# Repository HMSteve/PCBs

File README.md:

# Eine Sammlung von PCBs

Hier finden sich Platinen fuer verschiedene Projekte.

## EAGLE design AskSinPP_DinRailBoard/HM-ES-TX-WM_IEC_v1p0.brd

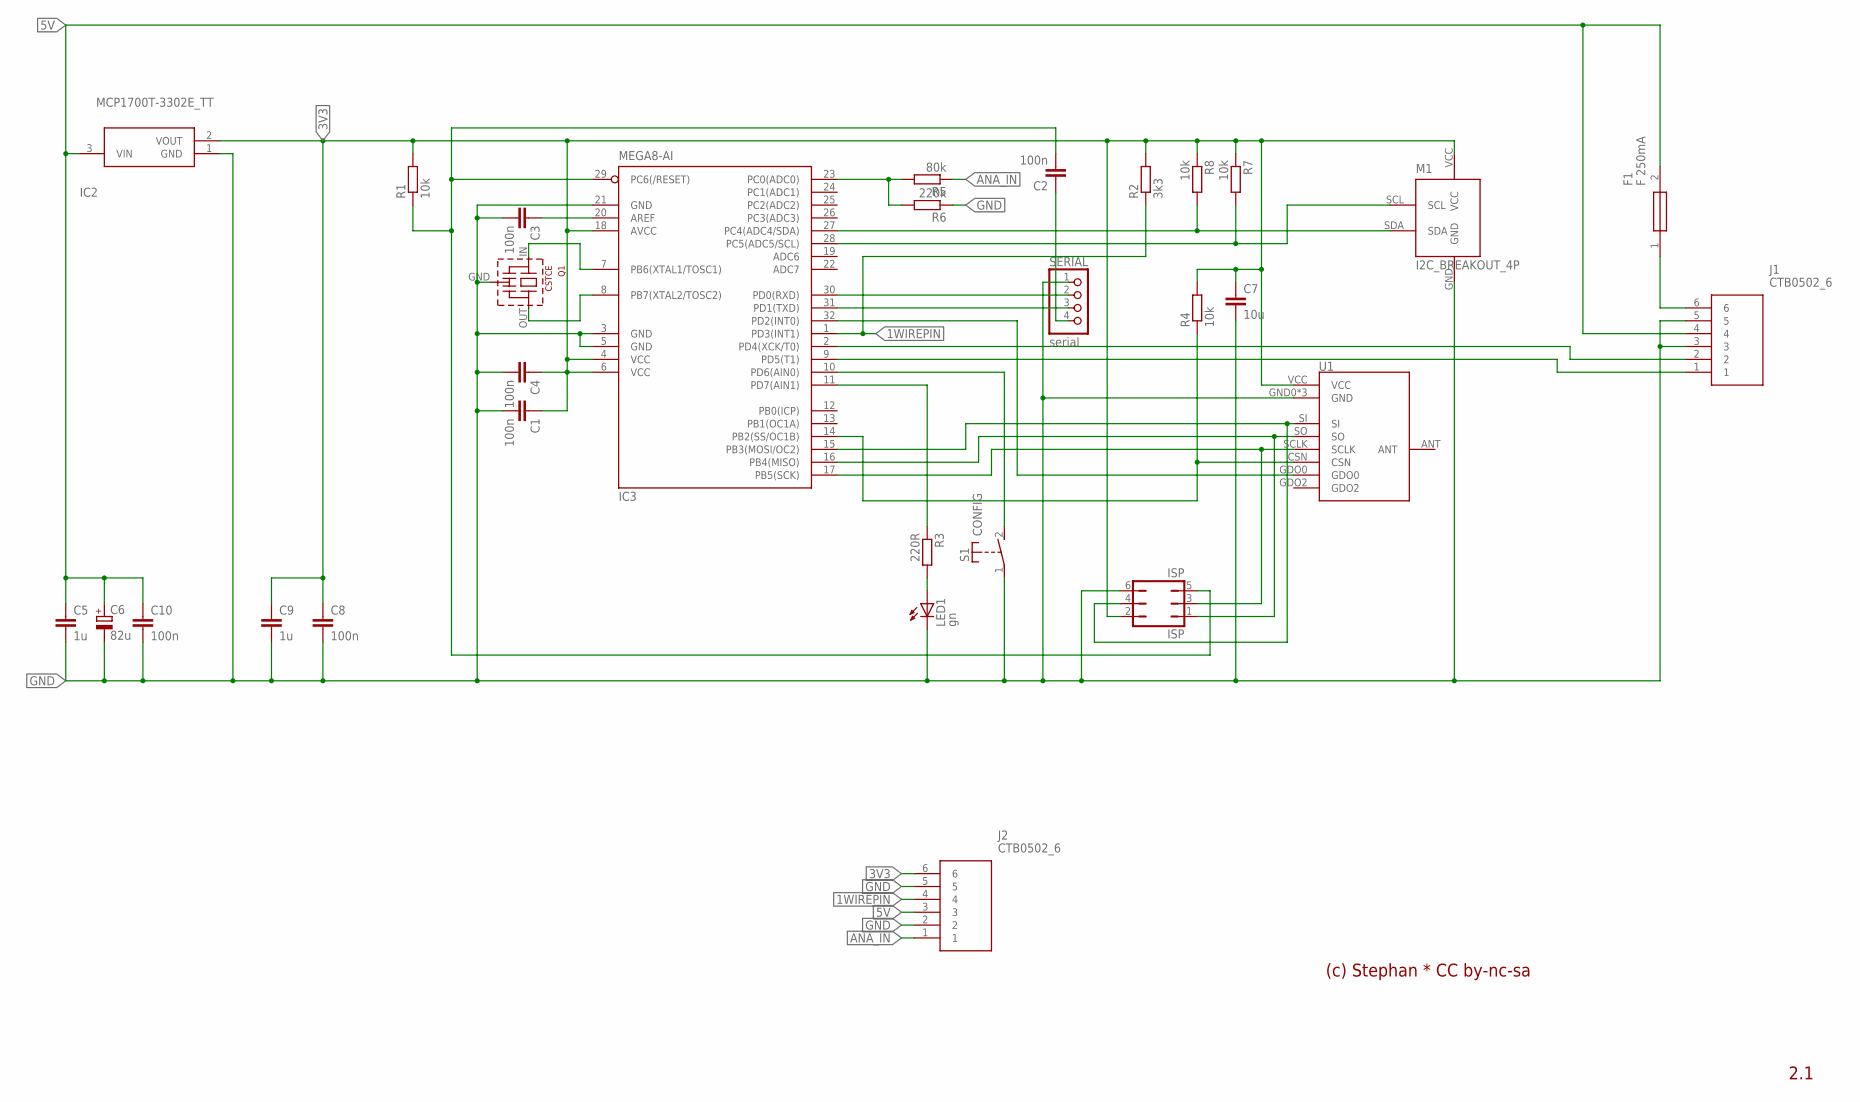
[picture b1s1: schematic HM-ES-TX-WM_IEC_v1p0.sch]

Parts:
C1, C2, C3, C4, C8, C10: 100n; C0805K
C5, C9: 1u; C0805K
C6: 82u; SANYO-OSCON_SMD_C6
C7: 10u; C0805K
F1: F 250mA; FUSC6125X279N
IC2: MCP1700T-3302E_TT; SOT95P237X112-3N
IC3: MEGA8-AI; TQFP32-08
ISP: ISP; JP3Q
J1, J2: CTB0502_6; CTB05026
LED1: gn; CHIPLED_0805
M1: I2C_BREAKOUT_4P
Q1: CSTCE
R1, R4, R7, R8: 10k; R0805W
R2: 3k3; R0805W
R3: 220R; R0805W
R5: 80k; R0805W
R6: 220k; R0805W
S1: CONFIG; SMDSWITCH6X4
SERIAL: serial; 1X04
U1: CC1101SMD; CC1101-SMD

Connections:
1WIREPIN: IC3.1 (PD3(INT1)), J2.4, R2.1
3V3: C1.1, C4.1, C7.1, C8.1, C9.1, IC2.2 (VOUT), IC3.4 (VCC), IC3.6 (VCC), IC3.18 (AVCC), ISP.2, J2.6, M1.VCC, R1.2, R2.2, R4.2, R7.1, R8.1, U1.VCC
5V: C5.1, C6.+, C10.1, F1.2, IC2.3 (VIN), J1.4, J2.3
ANA_IN: J2.1, R5.1
ANA_IN_PIN: IC3.23 (PC0(ADC0)), R5.2, R6.2
AREF: C3.1, IC3.20 (AREF)
BTNPIN: IC3.10 (PD6(AIN0)), S1.2 (S)
CSN: IC3.14 (PB2(SS/OC1B)), R4.1, U1.CSN
D4: IC3.2 (PD4(XCK/T0)), J1.2
D5: IC3.9 (PD5(T1)), J1.1
DTR: C2.1, SERIAL.4
GDO0: IC3.32 (PD2(INT0)), U1.GDO0
GND: C1.2, C3.2, C4.2, C5.2, C6.-, C7.2, C8.2, C9.2, C10.2, IC2.1 (GND), IC3.3 (GND), IC3.5 (GND), IC3.21 (GND), ISP.6, J1.3, J1.5, J2.2, J2.5, LED1.C, M1.GND, Q1.GND, R6.1, S1.1, SERIAL.1, U1.GND0 (GND), U1.GND1 (GND), U1.GND2 (GND)
LED1: LED1.A, R3.2
LEDPIN: IC3.11 (PD7(AIN1)), R3.1
MISO: IC3.16 (PB4(MISO)), ISP.1, U1.SO
MOSI: IC3.15 (PB3(MOSI/OC2)), ISP.4, U1.SI
RESET: C2.2, IC3.29 (PC6(/RESET)), ISP.5, R1.1
RXD: IC3.30 (PD0(RXD)), SERIAL.2
SCL: IC3.28 (PC5(ADC5/SCL)), M1.SCL, R7.2
SCLK: IC3.17 (PB5(SCK)), ISP.3, U1.SCLK
SDA: IC3.27 (PC4(ADC4/SDA)), M1.SDA, R8.2
TXD: IC3.31 (PD1(TXD)), SERIAL.3
VIN: F1.1, J1.6
XTAL1: IC3.7 (PB6(XTAL1/TOSC1)), Q1.IN
XTAL2: IC3.8 (PB7(XTAL2/TOSC2)), Q1.OUT

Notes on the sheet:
2.1
(c) Stephan * CC by-nc-sa

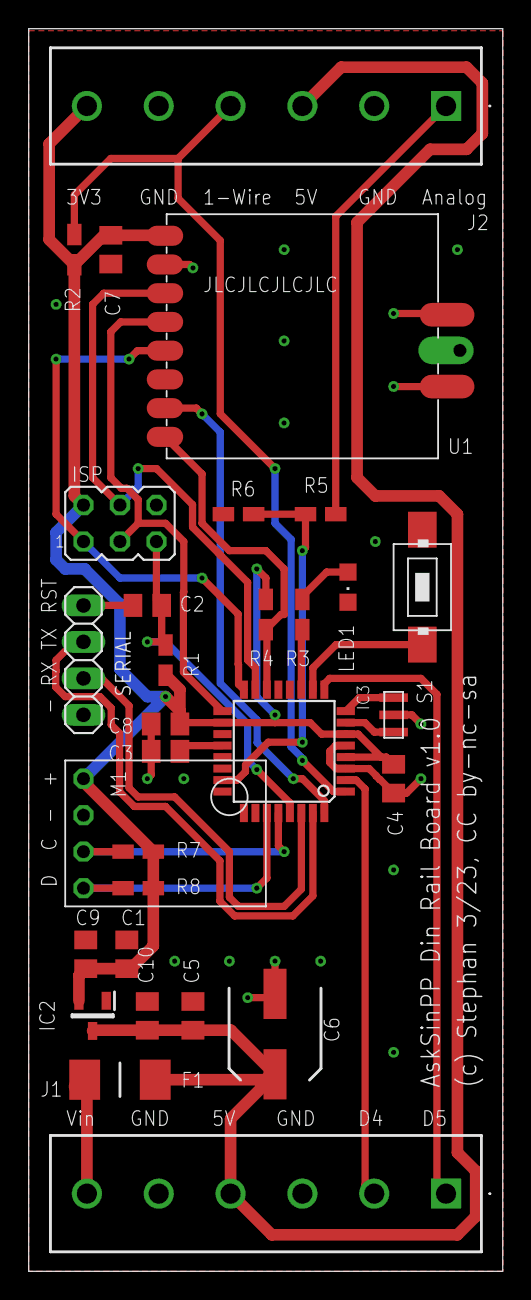
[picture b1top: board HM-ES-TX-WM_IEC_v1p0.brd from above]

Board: 2 copper layers, 33.0 x 86.5 mm, 30 parts (0 on the bottom side), 26 nets.

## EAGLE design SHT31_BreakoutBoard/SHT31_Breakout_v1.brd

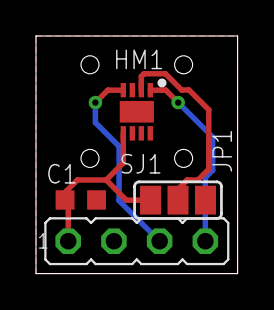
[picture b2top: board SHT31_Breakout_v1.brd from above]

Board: 2 copper layers, 11.2 x 13.2 mm, 4 parts (0 on the bottom side), 5 nets.

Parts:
C1: 100n; C0603K
HM1: SHT31-DIS-F2.5KS; SON50P250X250X90-9N
JP1: JP4
SJ1: AddrSel; SJ_2

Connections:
3V3: C1.1, HM1.5, JP1.1, SJ1.3
ADDR: HM1.2, SJ1.2
GND: C1.2, HM1.7, HM1.8, HM1.9, JP1.2, SJ1.1
SCL: HM1.4, JP1.3
SDA: HM1.1, JP1.4

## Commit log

2020-07-16 Erweiterung Readme
2020-07-16 Readme updated
2020-07-26 AskSinPP Universal Board added
2020-07-26 Images updated
2020-08-10 Added SGPC3 Breakout Board
2021-05-21 SCD41 breakout added
2021-06-16 CC1101 Mini Testbench added
2021-12-29 SHT31 breakout added
2023-04-07 Din Rail Board added
2023-04-07 pics added
2023-04-08 LDO part number corrected

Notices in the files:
AskSinPP_DinRailBoard/HM-ES-TX-WM_IEC_v1p0.brd:
(c) Stephan 3/23, CC by-nc-sa
parts and their libraries:
modules: Released under the Creative Commons Attribution 4.0 International License: http://creativecommons.org/licenses/by/4.0
